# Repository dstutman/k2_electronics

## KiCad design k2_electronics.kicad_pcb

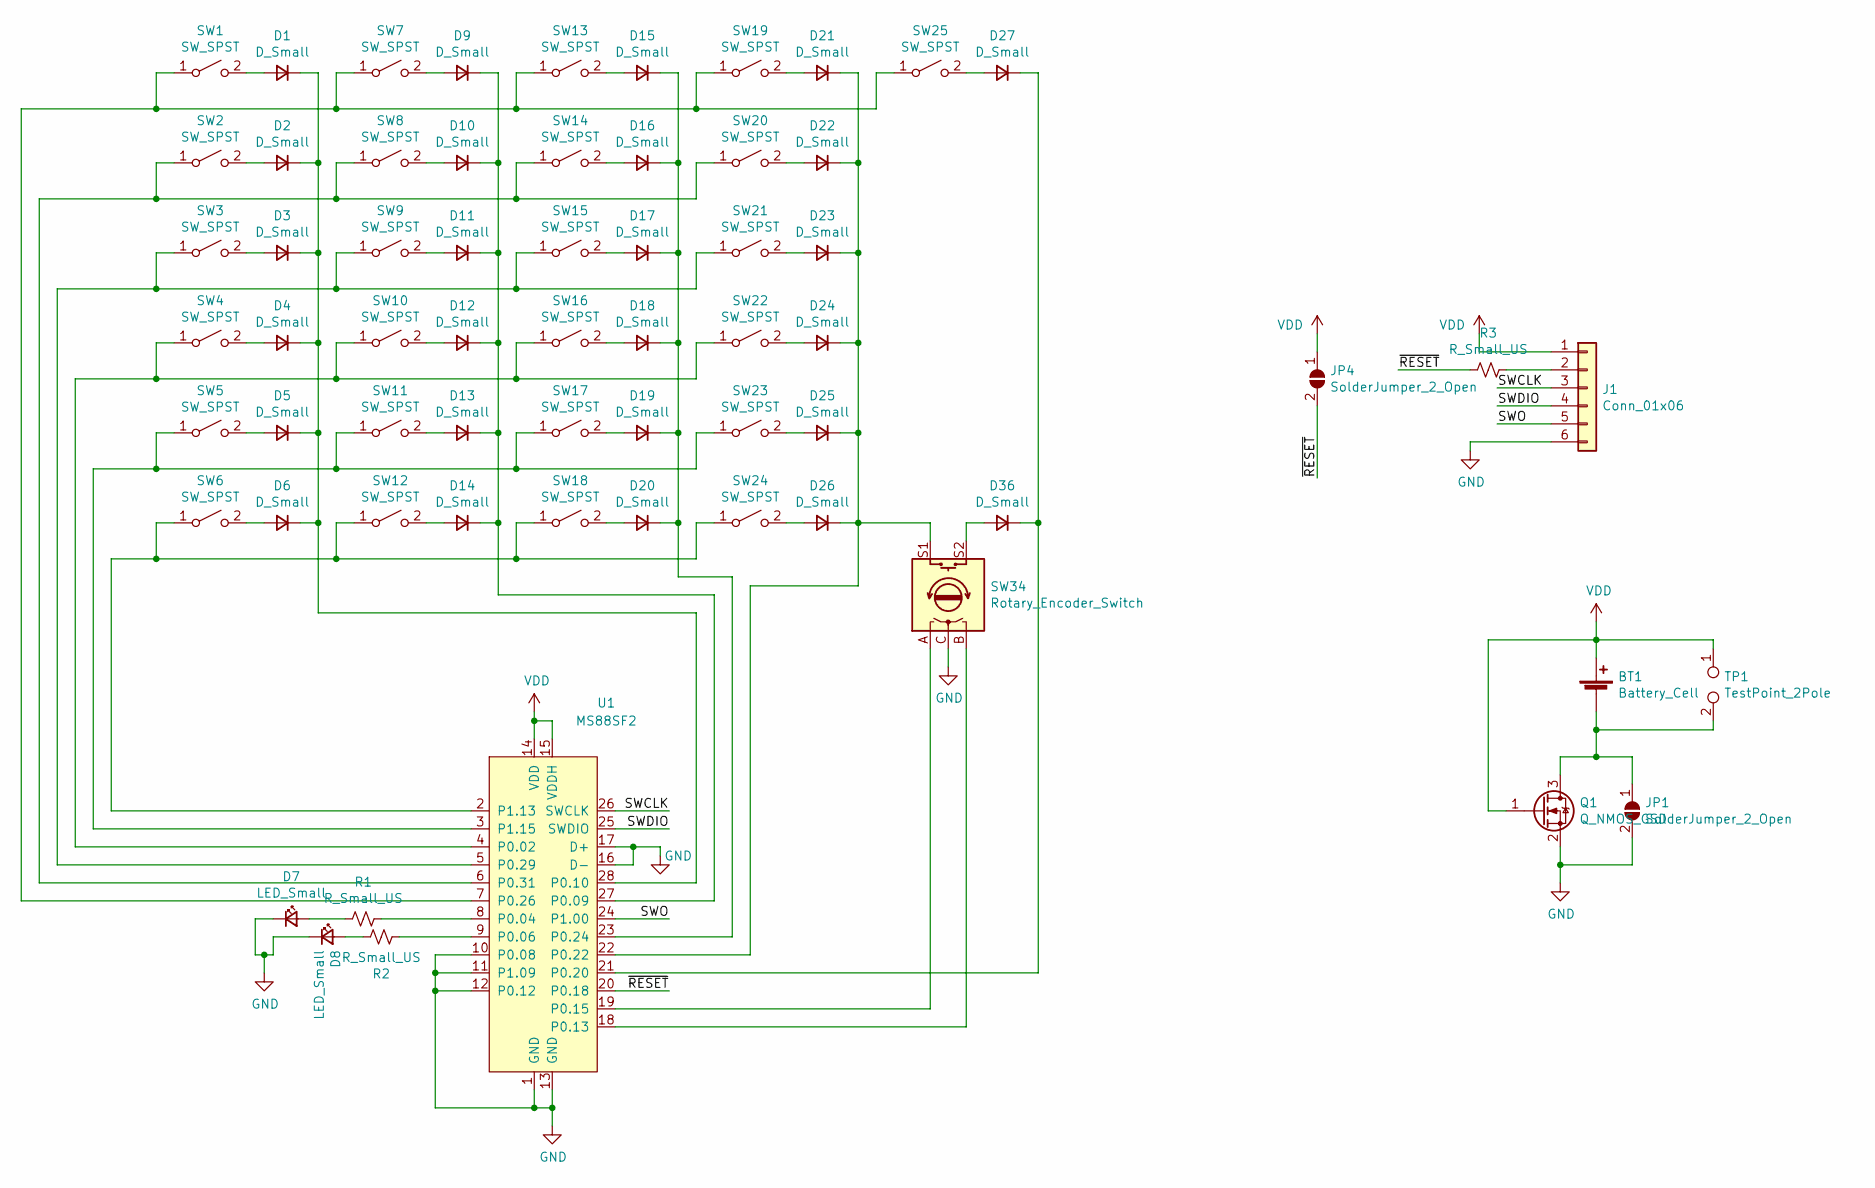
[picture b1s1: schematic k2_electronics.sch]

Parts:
BT1: Battery_Cell; BatteryHolder_Keystone_3009_1x2450_reversible
D1, D2, D3, D4, D5, D6, D9, D10, D11, D12, D13, D14, D15, D16, D17, D18, D19, D20, D21, D22, D23, D24, D25, D26, D27, D36: D_Small; D_SOD-123F_reversible
D7, D8: LED_Small; LED_0603_1608Metric_Pad1.05x0.95mm_HandSolder_reversible
J1: Conn_01x06; PinHeader_1x06_P2.54mm_Horizontal
JP1, JP4: SolderJumper_2_Open; SolderJumper-2_P1.3mm_Open_Pad1.0x1.5mm_reversible
Q1: Q_NMOS_GSD; SOT-23_Handsoldering_reversible
R1, R2, R3: R_Small_US; R_0603_1608Metric_Pad0.98x0.95mm_HandSolder_reversible
SW1, SW2, SW3, SW4, SW5, SW6, SW7, SW8, SW9, SW10, SW11, SW12, SW13, SW14, SW15, SW16, SW17, SW18, SW19, SW20, SW21, SW22, SW23, SW24, SW25: SW_SPST; SW_PG1350_reversible
SW34: Rotary_Encoder_Switch; RotaryEncoder_Alps_EC11E-Switch_Vertical_H20mm
TP1: TestPoint_2Pole; TestPoint_2Pads_Pitch2.54mm_Drill0.8mm
U1: MS88SF2; MS88F2_reversible

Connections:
/SWCLK: J1.3, U1.26 (SWCLK)
/SWDIO: J1.4, U1.25 (SWDIO)
/SWO: J1.5, U1.24 (P1.00)
/~RESET: JP4.2 (B), R3.1, U1.20 (P0.18)
GND: D7.1 (K), D8.1 (K), J1.6, JP1.2 (B), Q1.2 (S), SW34.C, U1.1 (GND), U1.10 (P0.08), U1.11 (P1.09), U1.12 (P0.12), U1.13 (GND), U1.16 (D-), U1.17 (D+)
unnamed: BT1.2 (-), JP1.1 (A), Q1.3 (D), TP1.2
unnamed: D1.1 (K), D2.1 (K), D3.1 (K), D4.1 (K), D5.1 (K), D6.1 (K), U1.28 (P0.10)
unnamed: D1.2 (A), SW1.2 (B)
unnamed: D2.2 (A), SW2.2 (B)
unnamed: D3.2 (A), SW3.2 (B)
unnamed: D4.2 (A), SW4.2 (B)
unnamed: D5.2 (A), SW5.2 (B)
unnamed: D6.2 (A), SW6.2 (B)
unnamed: D7.2 (A), R1.1
unnamed: D8.2 (A), R2.2
unnamed: D9.2 (A), SW7.2 (B)
unnamed: D9.1 (K), D10.1 (K), D11.1 (K), D12.1 (K), D13.1 (K), D14.1 (K), U1.27 (P0.09)
unnamed: D10.2 (A), SW8.2 (B)
unnamed: D11.2 (A), SW9.2 (B)
unnamed: D12.2 (A), SW10.2 (B)
unnamed: D13.2 (A), SW11.2 (B)
unnamed: D14.2 (A), SW12.2 (B)
unnamed: D15.1 (K), D16.1 (K), D17.1 (K), D18.1 (K), D19.1 (K), D20.1 (K), U1.23 (P0.24)
unnamed: D15.2 (A), SW13.2 (B)
unnamed: D16.2 (A), SW14.2 (B)
unnamed: D17.2 (A), SW15.2 (B)
unnamed: D18.2 (A), SW16.2 (B)
unnamed: D19.2 (A), SW17.2 (B)
unnamed: D20.2 (A), SW18.2 (B)
unnamed: D21.1 (K), D22.1 (K), D23.1 (K), D24.1 (K), D25.1 (K), D26.1 (K), SW34.S1, U1.22 (P0.22)
unnamed: D21.2 (A), SW19.2 (B)
unnamed: D22.2 (A), SW20.2 (B)
unnamed: D23.2 (A), SW21.2 (B)
unnamed: D24.2 (A), SW22.2 (B)
unnamed: D25.2 (A), SW23.2 (B)
unnamed: D26.2 (A), SW24.2 (B)
unnamed: D27.1 (K), D36.1 (K), U1.21 (P0.20)
unnamed: D27.2 (A), SW25.2 (B)
unnamed: D36.2 (A), SW34.S2
unnamed: J1.2, R3.2
unnamed: R1.2, U1.8 (P0.04)
unnamed: R2.1, U1.9 (P0.06)
unnamed: SW1.1 (A), SW7.1 (A), SW13.1 (A), SW19.1 (A), SW25.1 (A), U1.7 (P0.26)
unnamed: SW4.1 (A), SW10.1 (A), SW16.1 (A), SW22.1 (A), U1.4 (P0.02)
unnamed: SW5.1 (A), SW11.1 (A), SW17.1 (A), SW23.1 (A), U1.3 (P1.15)
unnamed: SW6.1 (A), SW12.1 (A), SW18.1 (A), SW24.1 (A), U1.2 (P1.13)
unnamed: SW2.1 (A), SW8.1 (A), SW14.1 (A), SW20.1 (A), U1.6 (P0.31)
unnamed: SW3.1 (A), SW9.1 (A), SW15.1 (A), SW21.1 (A), U1.5 (P0.29)
unnamed: SW34.A, U1.19 (P0.15)
unnamed: SW34.B, U1.18 (P0.13)
VDD: BT1.1 (+), J1.1, JP4.1 (A), Q1.1 (G), TP1.1, U1.14 (VDD), U1.15 (VDDH)

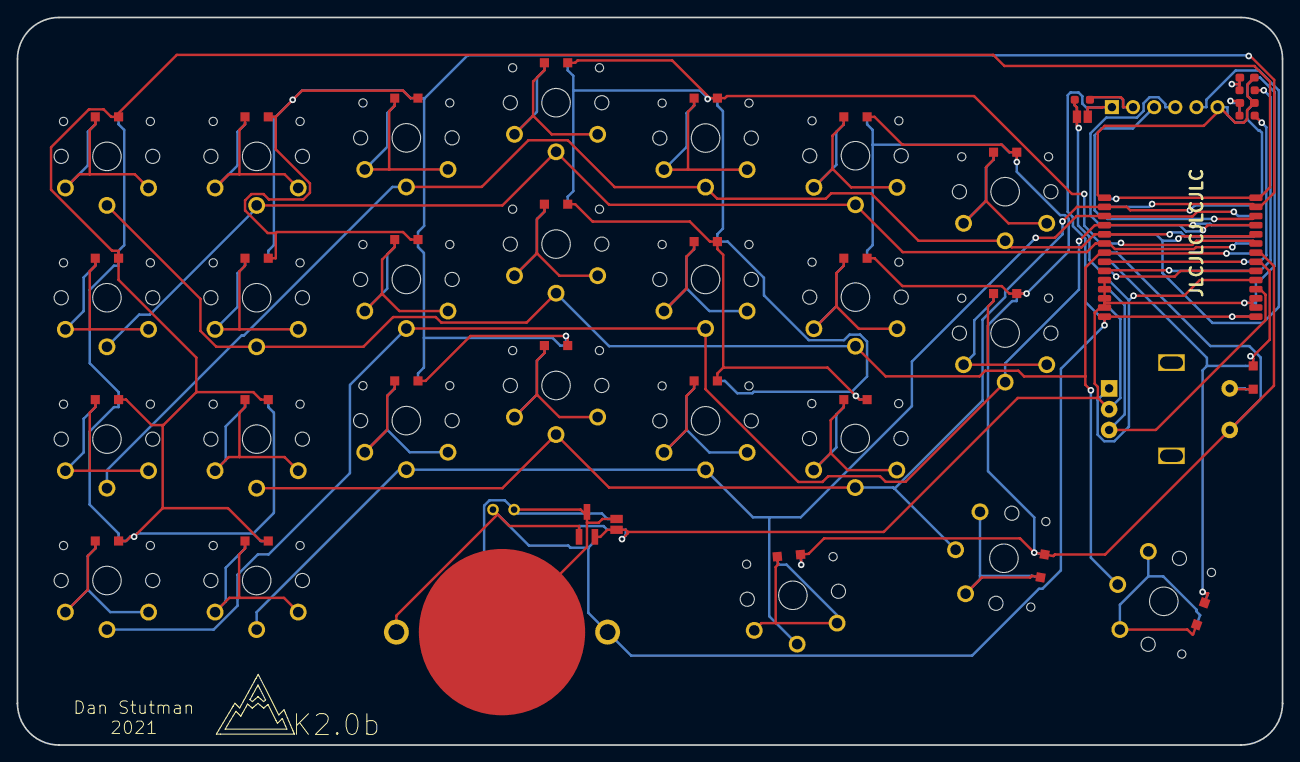
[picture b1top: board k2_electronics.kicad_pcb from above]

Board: 2 copper layers, 152.1 x 87.5 mm, 64 parts (0 on the bottom side), 51 nets.

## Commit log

2021-02-20 Component placement and autoroute
2021-02-21 Ensure all footprints reversible and touchup
2021-02-21 Prepare for the worst
2021-02-21 Store for deletions
2021-02-21 Reroute
2021-02-21 Switch to NPTH holes
2021-02-22 PCB mount
2021-04-06 Fix module footprint
2021-04-06 Add module model
2021-04-06 Improve module model
